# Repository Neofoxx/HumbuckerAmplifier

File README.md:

# HumbuckerAmplifier
An amplifier for humbucking pickups (like other popular brands). Just a bit cheaper and more versatile.

#### Render

#### Mounting

#### Schematic

## Description
This is an amplifier for humbucking pickups. It takes two coils, with one side of each connected to GND, and the other to the input. Take care to connect properly, otherwise you will get a noise amplifier :) (in-phase sound will cancel, and out-of-phase noise will amplify).

**Note, you need either a 4-wire pickup, or some soldering skills. You cannot use a series humbucker, or a parallel humbucker**

The curcuit uses a dual opamp, so you can play around with voicing without fear of power supply modulation distortion etc.

A TLV2170 will give great results, as will an MC33171. Other opamps like TL072 or TL062 will be *OK*, but in that case I suggest upping the voltage to 18V. Consult the schematic.

## Features

- Gain can be as high as you want, but be warned that amps usually have limited input headroom, so beyond some point "making it louder" will have a negative effect.

- The circuit is usable throught the batteries entire range. Works just find with power-switching on the output jack (TRS jack, short R (Bat-) and S (GND)).

- Since this is a one-sided board, it can be easily made at home.

- **REVERSE POLARITY PROTECTION**

- The circuit board should fit comfortably under a humbucker, but you can relocate it if you want to.

- Use desoldering braid to mount the PCB to the board (see pictures)

## Voicing
The circuit is quite versatile, as there are multiple positions prepared for mods & voicing.

### Basic voicing
Voicing can be done in these ways:

- Capacitors C3 and C4 define how lows are passed through. Small value == less lows, more highs. There reverse is true for Big values.

- Value of (R3+R8) and (R4+R5) define the "loading" of each coil. This defines the resonance peak. Think how a single coil "needs" 250k pots, and humbuckers need "500k" pots. Higher values will shift the resonance higher, and can produce "shrill" or ice pick-y sounds. Lower values will shift the resonance down, and make a more mellow, or muddy tone.

- The value of (R3+R8) and (R4+R5) doesn't have to be the same. C3 and C4 as well. Experiment with values, trust your ears.

- Gain is defined with R4 and R5. Gain = 1 + (R5/R2). Well, it also depends on (R3 and R8), but in practice you can just go with the simple forumla.

- C11 is there to help you if you go crazy with gain. A few pF is all you need usually.

### Advanced voicing
There are some footprints prepared for extra voicing. You can then connect a switch/push-pull pot/? between those footprints and GND, to spice things up.
Some examples /w speculation:
- C7 = 0ohm jumper, R9 = 220k. This will shift the resonance of one coil down. This can help spread the gain on higher frequencies more evenly.
- C10 = 2.2nF, R12 = 0ohm, This is like a selective filter. Should give you a bit of a bass boost.
- C8, C9, R10 and R11 are prepared just so you can do some funky stuff. Can also place something like a diode there, or inductors, etc. Dunno, go nuts.
- C7 = 0ohm, R9 = 0ohm. This will short a coil, and effectively give you a single coil with **GAIN**. But this also means no noise canceling, so YMMV.

#### But what about audio grade capacitors??
No amount of NOS PIO capacitors, carbon resistors and magic smoke in the form of vintage opamps will improve your sound as much as practice will.

## Files
* The Gerber files are in the HW/Gerbers directory
* The BOM is in the HW/ibom directory
* The schematic is here in the root directory

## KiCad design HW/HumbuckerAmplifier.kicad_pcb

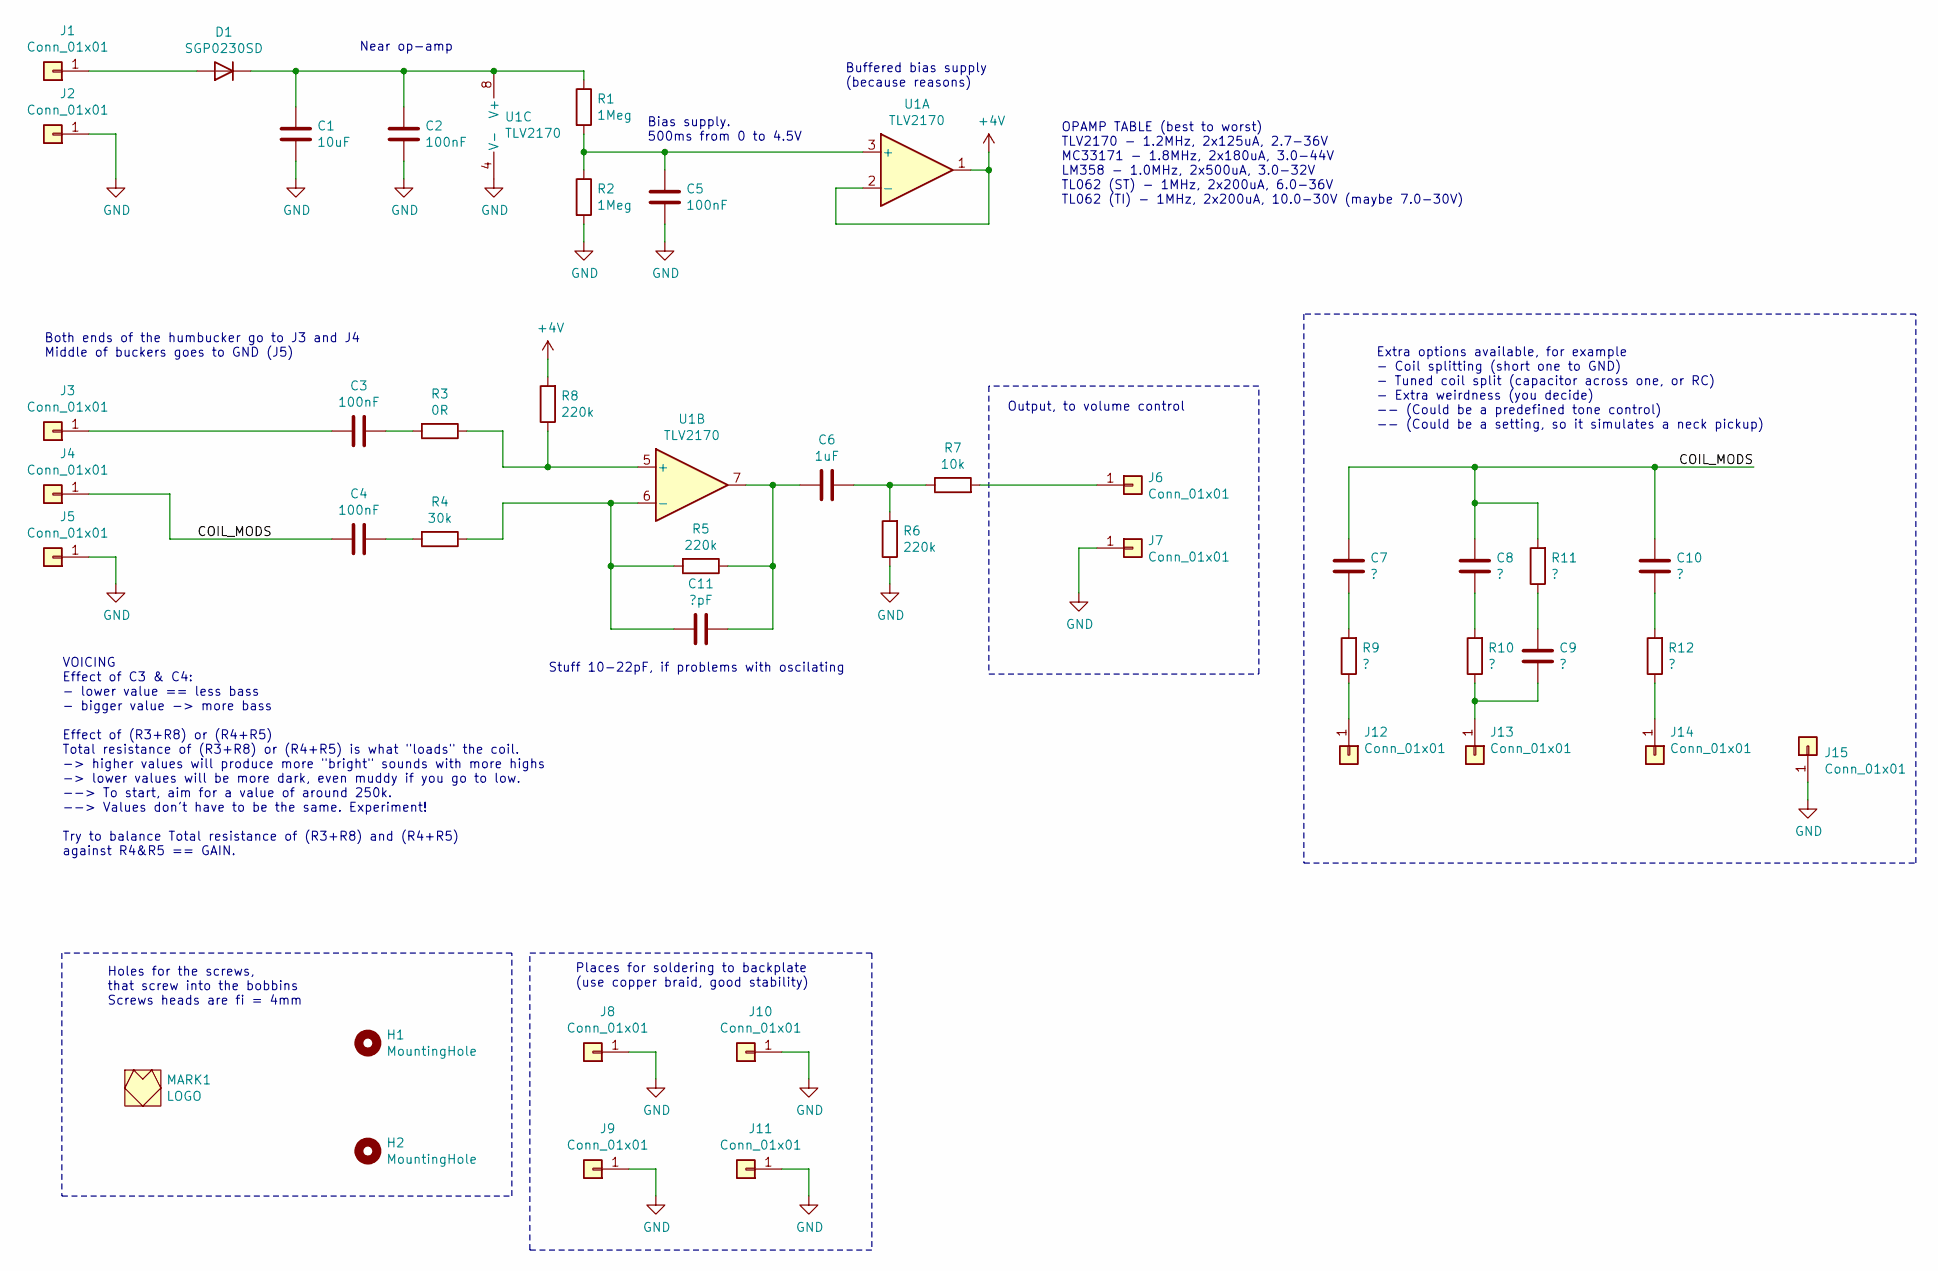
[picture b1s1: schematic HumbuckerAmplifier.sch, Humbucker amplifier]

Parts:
C1: 10uF; C_0805_2012Metric_Pad1.15x1.40mm_HandSolder
C2, C3, C4, C5: 100nF; C_0603_1608Metric_Pad1.05x0.95mm_HandSolder
C6: 1uF; C_0805_2012Metric_Pad1.15x1.40mm_HandSolder
C7, C8, C9, C10: ?; C_0603_1608Metric_Pad1.05x0.95mm_HandSolder
C11: ?pF; C_0603_1608Metric_Pad1.05x0.95mm_HandSolder
D1: SGP0230SD; D_SOD-323_HandSoldering
H1, H2: MountingHole; MountingHole_6mm
J1, J2, J3, J4, J5, J6, J7, J8, J9, J10, J11, J12, J13, J14, J15: Conn_01x01; SolderPad_2x3mm
MARK1: LOGO; FOX_LOGO_MASK
R1, R2: 1Meg; R_0603_1608Metric_Pad1.05x0.95mm_HandSolder
R3: 0R; R_0603_1608Metric_Pad1.05x0.95mm_HandSolder
R4: 30k; R_0603_1608Metric_Pad1.05x0.95mm_HandSolder
R5, R6, R8: 220k; R_0603_1608Metric_Pad1.05x0.95mm_HandSolder
R7: 10k; R_0603_1608Metric_Pad1.05x0.95mm_HandSolder
R9, R10, R11, R12: ?; R_0603_1608Metric_Pad1.05x0.95mm_HandSolder
U1: TLV2170; SOIC-8_3.9x4.9mm_P1.27mm

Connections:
+4V: R8.2, U1.1, U1.2 (-)
/COIL_MODS: C4.2, C7.2, C8.2, C10.2, J4.1, R11.2
GND: C1.2, C2.2, C5.2, J2.1, J5.1, J7.1, J8.1, J9.1, J10.1, J11.1, J15.1, R2.2, R6.1, U1.4 (V-)
unnamed: C1.1, C2.1, D1.1 (K), R1.1, U1.8 (V+)
unnamed: C3.1, R3.2
unnamed: C3.2, J3.1
unnamed: C4.1, R4.2
unnamed: C5.1, R1.2, R2.1, U1.3 (+)
unnamed: C6.1, R6.2, R7.1
unnamed: C7.1, R9.2
unnamed: C8.1, R10.2
unnamed: C9.1, J13.1, R10.1
unnamed: C9.2, R11.1
unnamed: C10.1, R12.2
unnamed: C6.2, C11.1, R5.1, U1.7
unnamed: C11.2, R4.1, R5.2, U1.6 (-)
unnamed: D1.2 (A), J1.1
unnamed: J6.1, R7.2
unnamed: J12.1, R9.1
unnamed: J14.1, R12.1
unnamed: R3.1, R8.1, U1.5 (+)

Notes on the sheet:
Holes for the screws, that screw into the bobbins Screws heads are fi = 4mm
Bias supply. 500ms from 0 to 4.5V
Near op-amp
Buffered bias supply (because reasons)
Both ends of the humbucker go to J3 and J4 Middle of buckers goes to GND (J5)
Places for soldering to backplate (use copper braid, good stability)
Extra options available, for example - Coil splitting (short one to GND) - Tuned coil split (capacitor across one, or RC) - Extra weirdness (you decide) -- (Could be a predefined tone control) -- (Could be a setting, so it simulates a neck pickup)
OPAMP TABLE (best to worst) TLV2170 - 1.2MHz, 2x125uA, 2.7-36V MC33171 - 1.8MHz, 2x180uA, 3.0-44V LM358 - 1.0MHz, 2x500uA, 3.0-32V TL062 (ST) - 1MHz, 2x200uA, 6.0-36V TL062 (TI) - 1MHz, 2x200uA, 10.0-30V (maybe 7.0-30V)
Stuff 10-22pF, if problems with oscilating
Output, to volume control
VOICING Effect of C3 & C4: - lower value == less bass - bigger value -> more bass Effect of (R3+R8) or (R4+R5) Total resistance of (R3+R8) or (R4+R5) is what "loads" the coil. -> higher values will produce more "bright" sounds with more highs -> lower values will be more dark, even muddy if you go 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

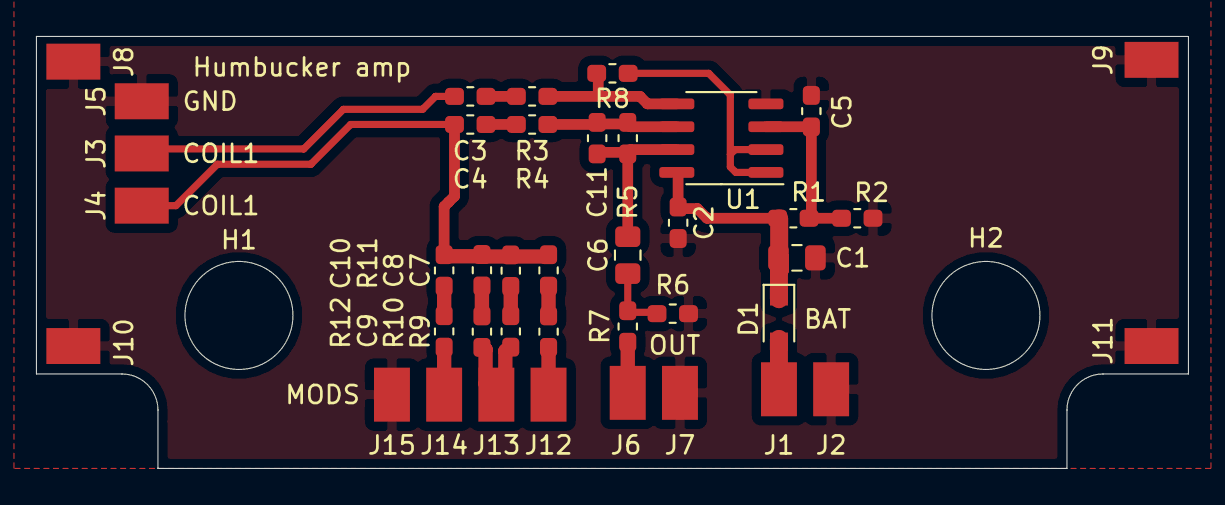
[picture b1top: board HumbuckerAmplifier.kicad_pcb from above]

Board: 2 copper layers, 64.0 x 24.0 mm, 43 parts (0 on the bottom side), 21 nets.

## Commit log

2021-03-13 Add docs & info
